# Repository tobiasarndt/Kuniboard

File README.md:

# Kuniboard
Wireless Split Keyboard with Trackpoint Support. WIP
Features:
* Column stagger and splay
* 42 keys, with option to snap off the outer pinky columns for a 36 key layout.
* Halfs can connect with magnets for transport
* MIP display on one half, trackpoint on other
* Halfes attach together with magnets for transportation. When attached, power is cut with a magnet switch.
* Overcharge and Underdischarge protection

[ZMK config](https://github.com/tobiasarndt/zmk-config)
## Finished Keyboard

## First Case Prototype

## Fist PCB Prototype
Ordered, waiting for PCBs to arrive

## Keyboard mascot Kunibert

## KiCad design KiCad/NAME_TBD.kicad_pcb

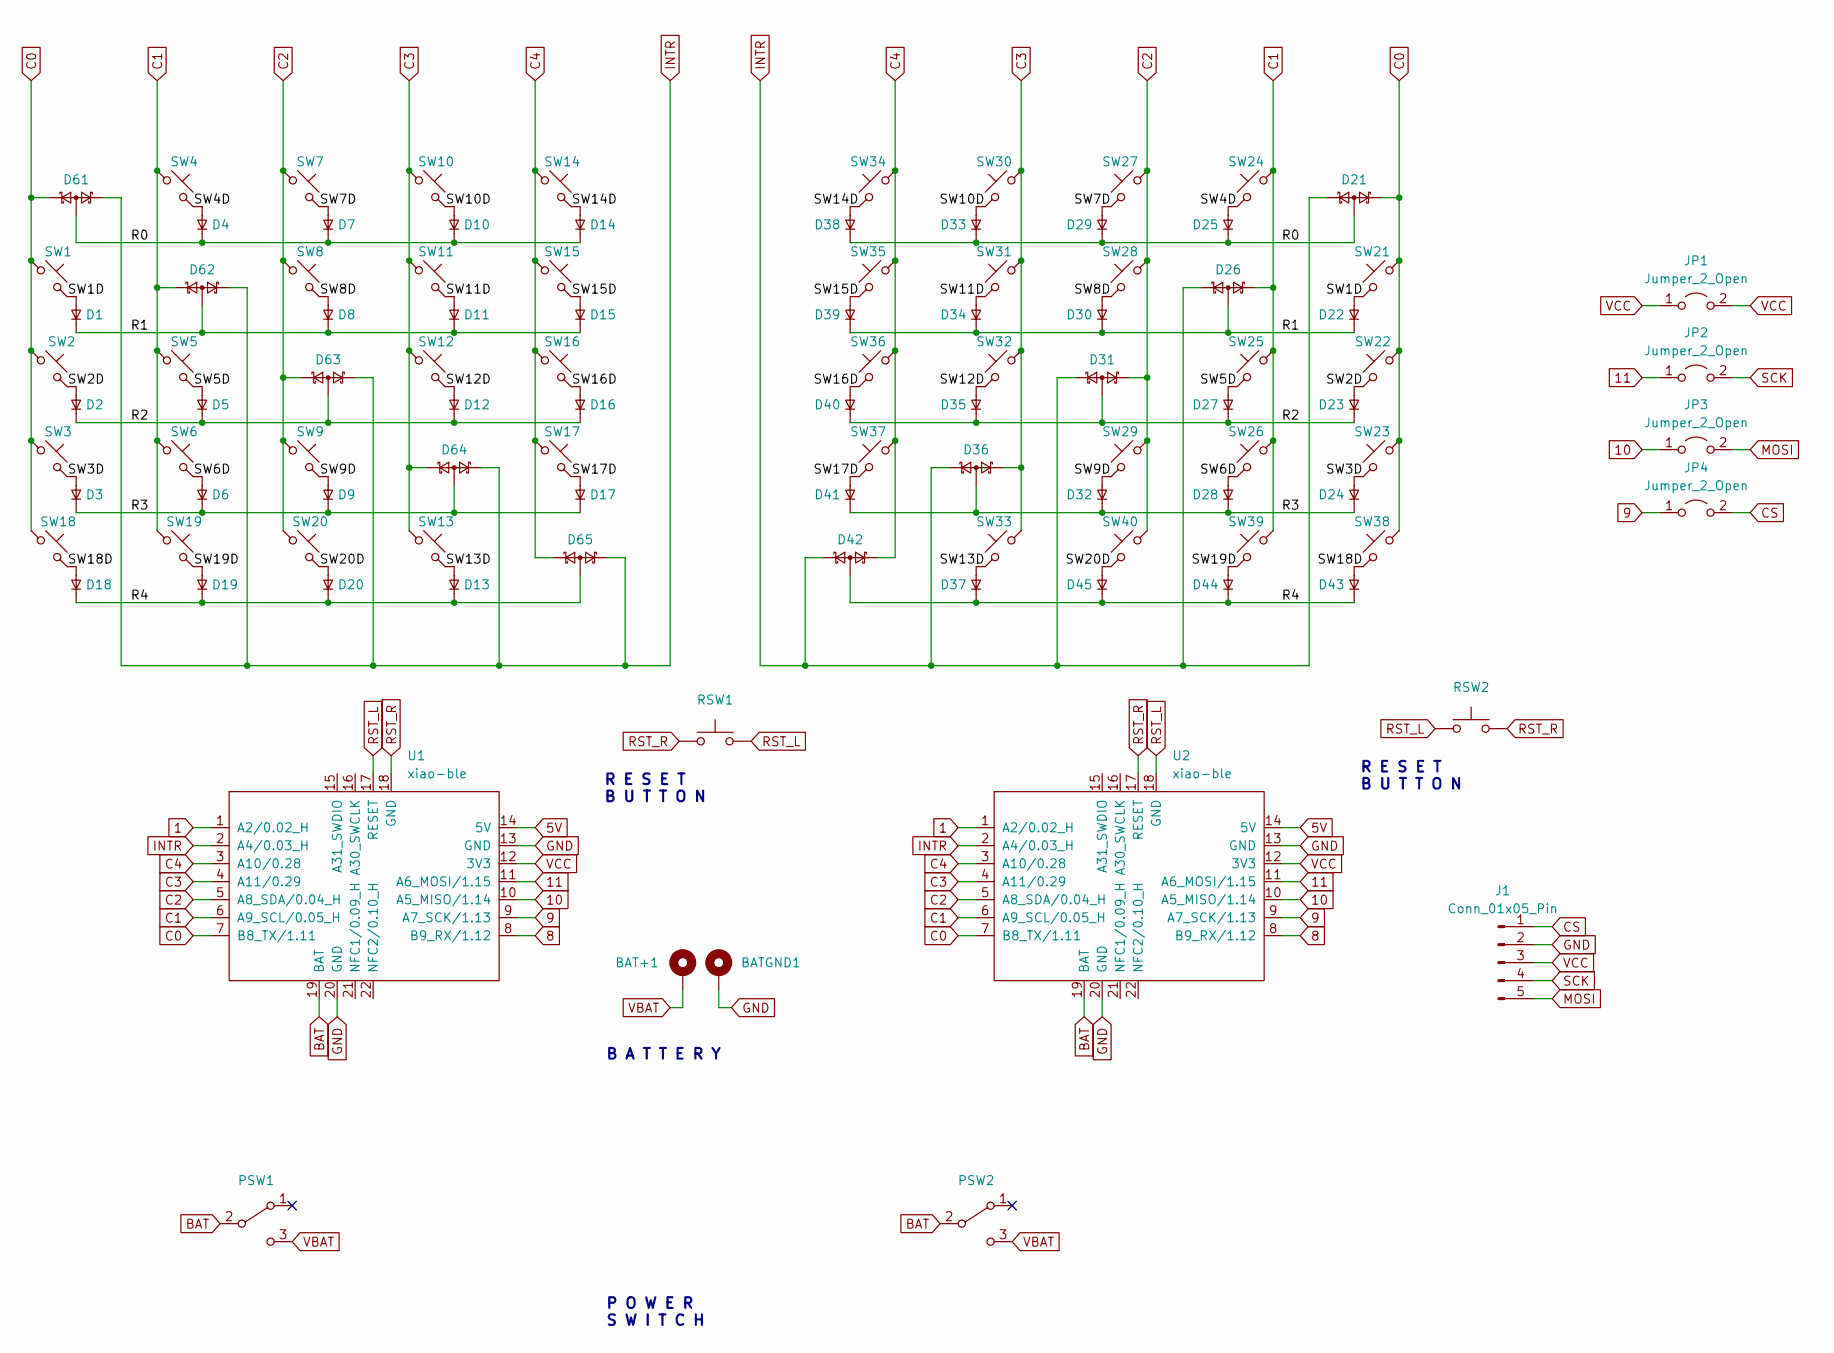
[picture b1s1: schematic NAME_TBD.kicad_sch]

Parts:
BAT+1: +; BatteryPad
BATGND1: -; BatteryPad
D1, D2, D3, D4, D5, D6, D7, D8, D9, D10, D11, D12, D13, D14, D15, D16, D17, D18, D19, D20, D22, D23, D24, D25, D27, D28, D29, D30, D32, D33, D34, D35, D37, D38, D39, D40, D41, D43, D44, D45: 1N4148W; D_SOD-123
D21, D26, D31, D36, D42, D61, D62, D63, D64, D65: BAT54A; SOT-23
J1: Conn_01x05_Pin; nice!view
JP1, JP2, JP3, JP4: Jumper_2_Open; SolderJumper-2_P1.3mm_Open_TrianglePad1.0x1.5mm
PSW1, PSW2: SW_SPDT; MSK12C02
RSW1, RSW2: SW_Push; SKHLLCA010
SW1, SW4, SW5, SW6, SW7, SW8, SW9, SW10, SW11, SW12, SW13, SW14, SW15, SW16, SW17, SW18, SW19, SW20, SW24, SW25, SW26, SW27, SW28, SW29, SW30, SW31, SW32, SW33, SW34, SW35, SW36, SW37, SW38, SW39, SW40: SW_Push_45deg; SW_Hotswap_Kailh_Choc_V1V2
SW2, SW3, SW21, SW22, SW23: SW_Hotswap_Kailh_Choc_V1V2
U1, U2: xiao-ble; xiao-ble-smd-cutout

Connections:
1: U1.1 (A2/0.02_H), U2.1 (A2/0.02_H)
5V: U1.14 (5V), U2.14 (5V)
8: U1.8 (B9_RX/1.12), U2.8 (B9_RX/1.12)
9: JP4.1 (A), U1.9 (A7_SCK/1.13), U2.9 (A7_SCK/1.13); also elsewhere on the board
10: JP3.1 (A), U1.10 (A5_MISO/1.14), U2.10 (A5_MISO/1.14); also elsewhere on the board
11: JP2.1 (A), U1.11 (A6_MOSI/1.15), U2.11 (A6_MOSI/1.15); also elsewhere on the board
/R0: D4.1 (K), D7.1 (K), D10.1 (K), D14.1 (K), D21.2, D25.1 (K), D29.1 (K), D33.1 (K), D38.1 (K), D61.2
/R1: D1.1 (K), D8.1 (K), D11.1 (K), D15.1 (K), D22.1 (K), D26.2, D30.1 (K), D34.1 (K), D39.1 (K), D62.2
/R2: D2.1 (K), D5.1 (K), D12.1 (K), D16.1 (K), D23.1 (K), D27.1 (K), D31.2, D35.1 (K), D40.1 (K), D63.2
/R3: D3.1 (K), D6.1 (K), D9.1 (K), D17.1 (K), D24.1 (K), D28.1 (K), D32.1 (K), D36.2, D41.1 (K), D64.2
/R4: D13.1 (K), D18.1 (K), D19.1 (K), D20.1 (K), D37.1 (K), D42.2, D43.1 (K), D44.1 (K), D45.1 (K), D65.2
/SW1D: D1.2 (A), D22.2 (A), SW1.2, SW21.2
/SW2D: D2.2 (A), D23.2 (A), SW2.2, SW22.2
/SW3D: D3.2 (A), D24.2 (A), SW3.2, SW23.2
/SW4D: D4.2 (A), D25.2 (A), SW4.2, SW24.2
/SW5D: D5.2 (A), D27.2 (A), SW5.2, SW25.2
/SW6D: D6.2 (A), D28.2 (A), SW6.2, SW26.2
/SW7D: D7.2 (A), D29.2 (A), SW7.2, SW27.2
/SW8D: D8.2 (A), D30.2 (A), SW8.2, SW28.2
/SW9D: D9.2 (A), D32.2 (A), SW9.2, SW29.2
/SW10D: D10.2 (A), D33.2 (A), SW10.2, SW30.2
/SW11D: D11.2 (A), D34.2 (A), SW11.2, SW31.2
/SW12D: D12.2 (A), D35.2 (A), SW12.2, SW32.2
/SW13D: D13.2 (A), D37.2 (A), SW13.2, SW33.2
/SW14D: D14.2 (A), D38.2 (A), SW14.2, SW34.2
/SW15D: D15.2 (A), D39.2 (A), SW15.2, SW35.2
/SW16D: D16.2 (A), D40.2 (A), SW16.2, SW36.2
/SW17D: D17.2 (A), D41.2 (A), SW17.2, SW37.2
/SW18D: D18.2 (A), D43.2 (A), SW18.2, SW38.2
/SW19D: D19.2 (A), D44.2 (A), SW19.2, SW39.2
/SW20D: D20.2 (A), D45.2 (A), SW20.2, SW40.2
BAT: PSW1.2 (B), PSW2.2 (B), U1.19 (BAT), U2.19 (BAT)
C0: D21.1, D61.1, SW1.1, SW2.1, SW3.1, SW18.1, SW21.1, SW22.1, SW23.1, SW38.1, U1.7 (B8_TX/1.11), U2.7 (B8_TX/1.11)
C1: D26.1, D62.1, SW4.1, SW5.1, SW6.1, SW19.1, SW24.1, SW25.1, SW26.1, SW39.1, U1.6 (A9_SCL/0.05_H), U2.6 (A9_SCL/0.05_H)
C2: D31.1, D63.1, SW7.1, SW8.1, SW9.1, SW20.1, SW27.1, SW28.1, SW29.1, SW40.1, U1.5 (A8_SDA/0.04_H), U2.5 (A8_SDA/0.04_H)
C3: D36.1, D64.1, SW10.1, SW11.1, SW12.1, SW13.1, SW30.1, SW31.1, SW32.1, SW33.1, U1.4 (A11/0.29), U2.4 (A11/0.29)
C4: D42.1, D65.1, SW14.1, SW15.1, SW16.1, SW17.1, SW34.1, SW35.1, SW36.1, SW37.1, U1.3 (A10/0.28), U2.3 (A10/0.28)
CS: J1.1, JP4.2 (B); also elsewhere on the board
GND: BATGND1.1, J1.2, U1.13 (GND), U1.20 (GND), U2.13 (GND), U2.20 (GND)
INTR: D21.3, D26.3, D31.3, D36.3, D42.3, D61.3, D62.3, D63.3, D64.3, D65.3, U1.2 (A4/0.03_H), U2.2 (A4/0.03_H)
MOSI: J1.5, JP3.2 (B); also elsewhere on the board
RST_L: RSW1.2, RSW2.1, U1.17 (RESET), U2.18 (GND)
RST_R: RSW1.1, RSW2.2, U1.18 (GND), U2.17 (RESET)
SCK: J1.4, JP2.2 (B); also elsewhere on the board
VBAT: BAT+1.1, PSW1.3 (C), PSW2.3 (C)
VCC: J1.3, JP1.1 (A), JP1.2 (B), U1.12 (3V3), U2.12 (3V3); also elsewhere on the board

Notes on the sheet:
P O W E R S W I T C H
B A T T E R Y
R E S E T B U T T O N

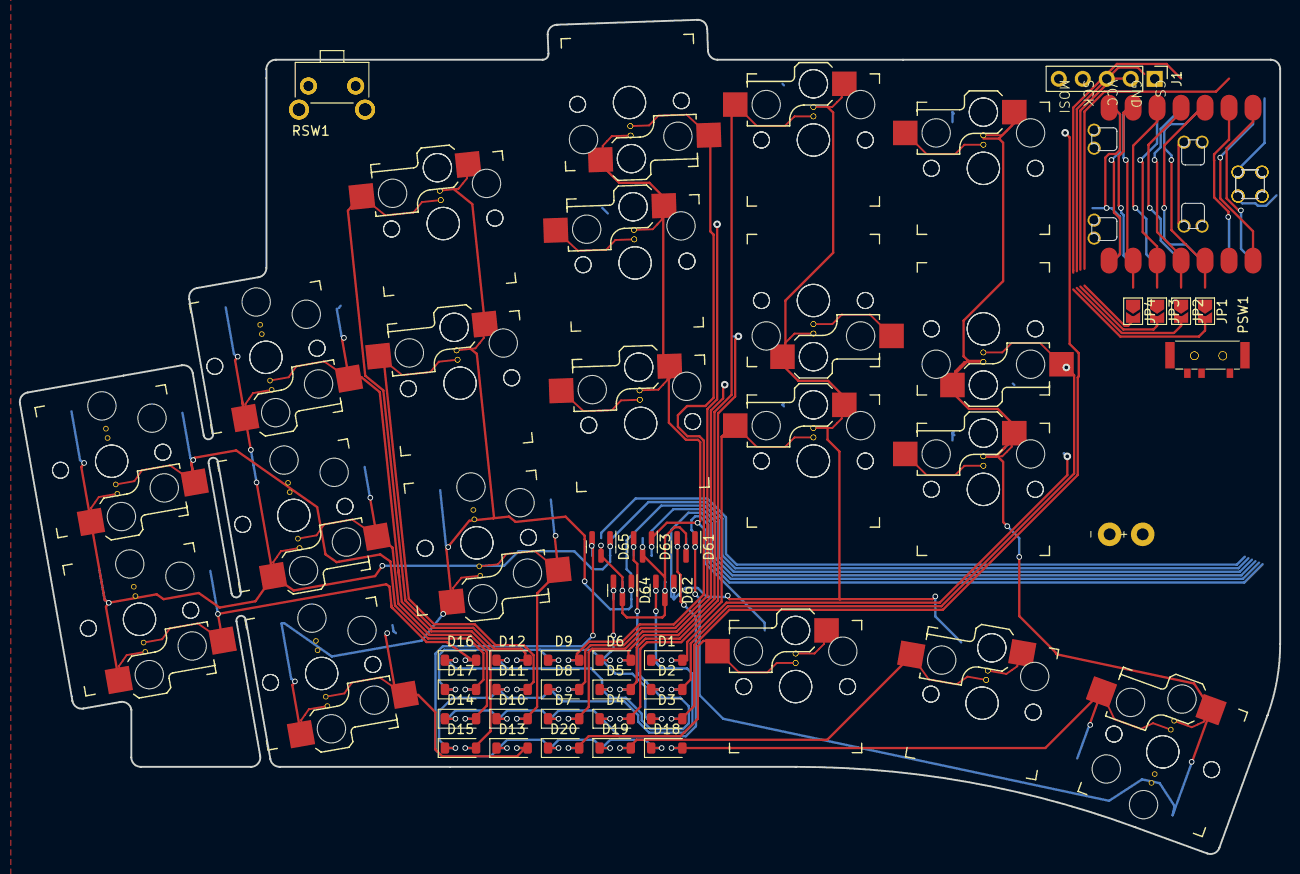
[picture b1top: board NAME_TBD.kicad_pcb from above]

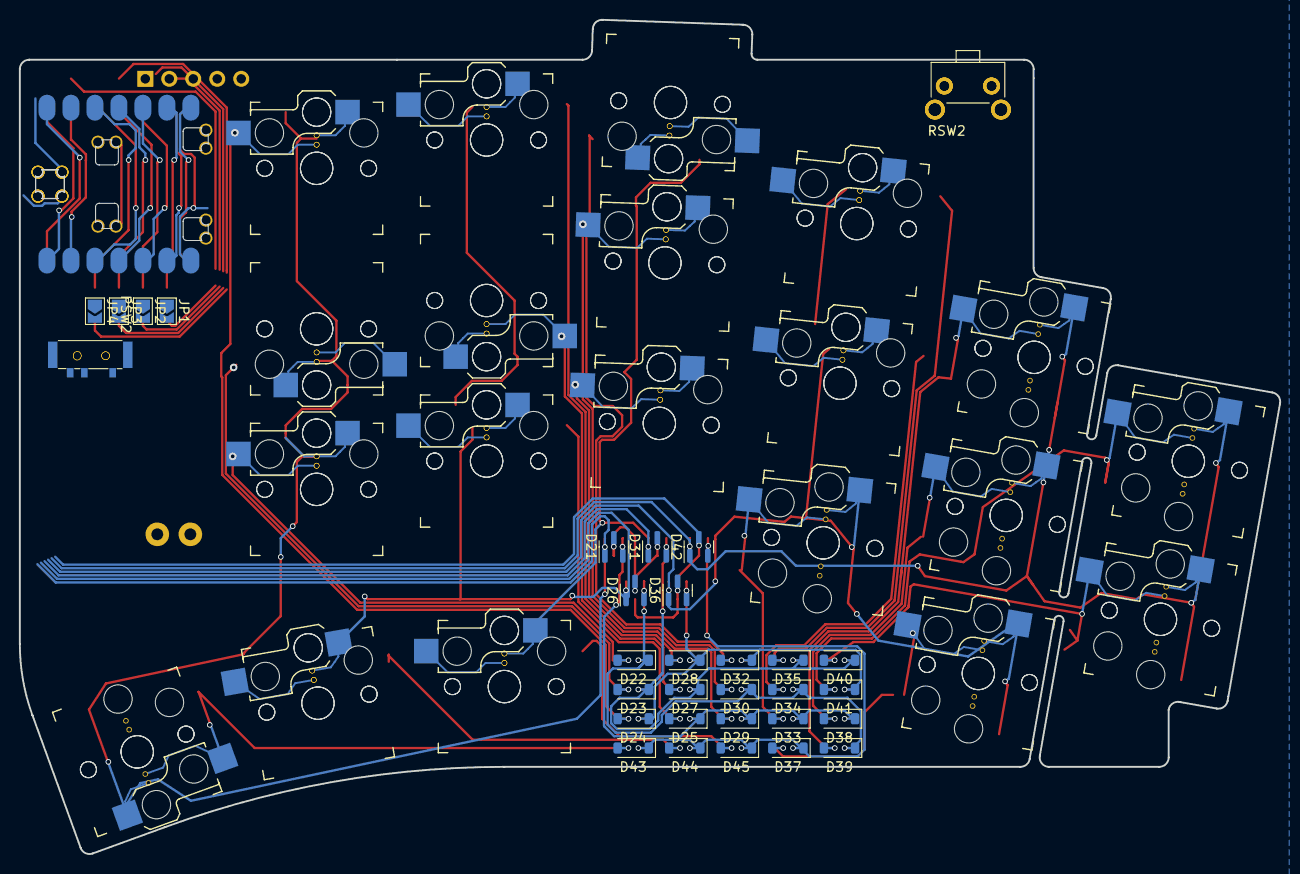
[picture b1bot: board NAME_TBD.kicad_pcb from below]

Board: 2 copper layers, 133.5 x 88.3 mm, 107 parts (52 on the bottom side), 46 nets.

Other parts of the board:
JP1#2, JP2#2, JP3#2, JP4#2: Jumper_2_Open; SolderJumper-2_P1.3mm_Open_TrianglePad1.0x1.5mm

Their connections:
9: JP4#2.1 (A); also elsewhere on the board
10: JP3#2.1 (A); also elsewhere on the board
11: JP2#2.1 (A); also elsewhere on the board
CS: JP4#2.2 (B); also elsewhere on the board
MOSI: JP3#2.2 (B); also elsewhere on the board
SCK: JP2#2.2 (B); also elsewhere on the board
VCC: JP1#2.1 (A), JP1#2.2 (B); also elsewhere on the board

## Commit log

2023-08-27 Changed spacing
2023-11-04 add kicad files
2023-11-25 pcb done with mascot
2023-11-25 moved lig
2026-04-09 add exported case stl files
